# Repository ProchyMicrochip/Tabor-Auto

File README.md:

# Tabor-Auto
Program pro ovládání autíčka přes esp8266 webserver

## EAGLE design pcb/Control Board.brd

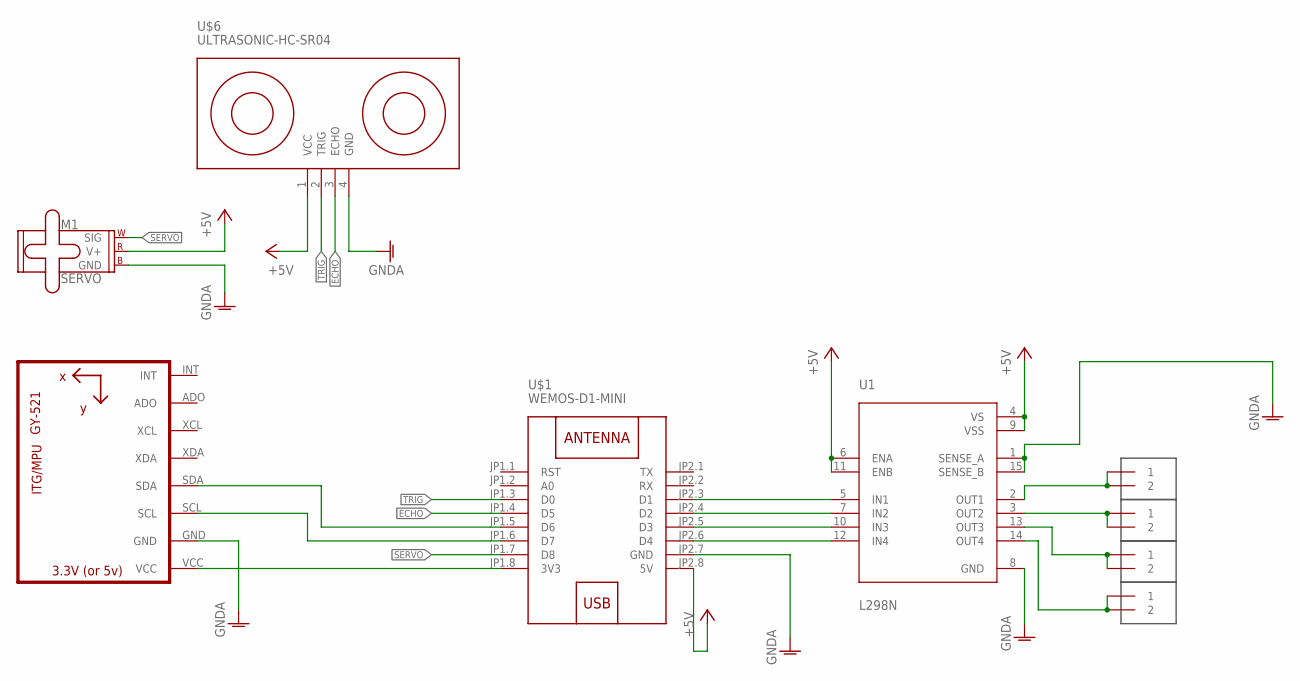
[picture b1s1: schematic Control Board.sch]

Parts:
M1: SERVO; 1X03
U1: L298N; TO127P2020X500X2100-15
U2: GY-521MPU6050; GY-521
U$1: WEMOS-D1-MINI
U$2, U$3, U$4, U$5: TERMINAL_2P; KF301-2P
U$6: ULTRASONIC-HC-SR04

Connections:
+5V: M1.2 (V+), U1.4 (VS), U1.6 (ENA), U1.9 (VSS), U1.11 (ENB), U$1.JP2.8 (5V), U$6.1 (VCC)
ECHO: U$1.JP1.4 (D5), U$6.3 (ECHO)
GNDA: M1.3 (GND), U1.1 (SENSE_A), U1.8 (GND), U1.15 (SENSE_B), U2.GND, U$1.JP2.7 (GND), U$6.4 (GND)
unnamed: U1.5 (IN1), U$1.JP2.3 (D1)
unnamed: U1.7 (IN2), U$1.JP2.4 (D2)
unnamed: U1.10 (IN3), U$1.JP2.5 (D3)
unnamed: U1.12 (IN4), U$1.JP2.6 (D4)
unnamed: U2.VCC, U$1.JP1.8 (3V3)
unnamed: U2.SCL, U$1.JP1.6 (D7)
unnamed: U2.SDA, U$1.JP1.5 (D6)
unnamed: U1.14 (OUT4), U$5.1, U$5.2
unnamed: U1.13 (OUT3), U$4.1, U$4.2
unnamed: U1.3 (OUT2), U$3.1, U$3.2
unnamed: U1.2 (OUT1), U$2.1, U$2.2
SERVO: M1.1 (SIG), U$1.JP1.7 (D8)
TRIG: U$1.JP1.3 (D0), U$6.2 (TRIG)

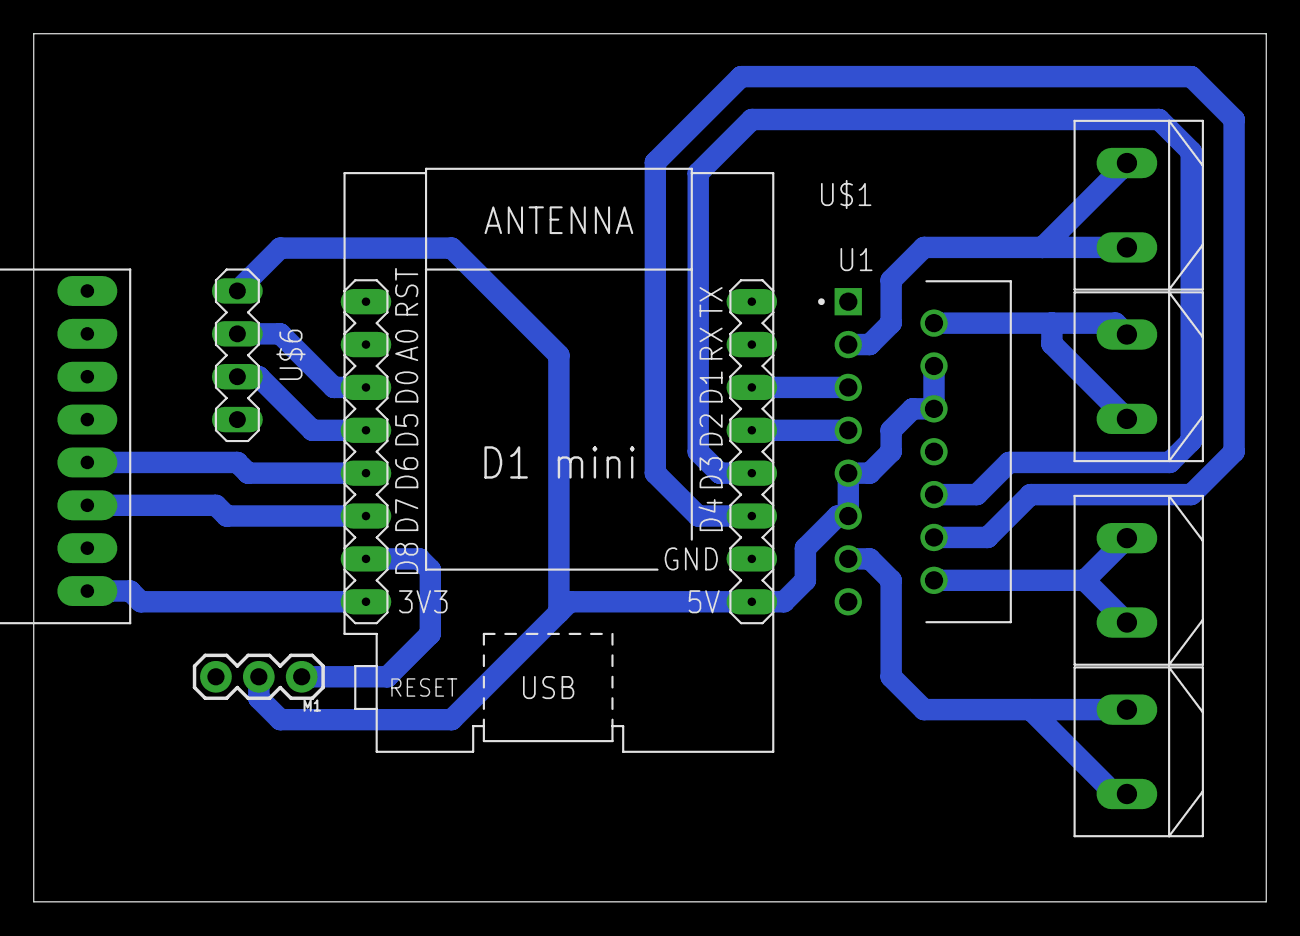
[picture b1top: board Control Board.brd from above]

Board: 2 copper layers, 73.0 x 51.4 mm, 9 parts (0 on the bottom side), 16 nets.

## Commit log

2023-07-07 Initial platformio commit

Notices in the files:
parts and their libraries:
SparkFun-Electromechanical: Licensing: Creative Commons ShareAlike 4.0 International - https://creativecommons.org/licenses/by-sa/4.0
diy-modules: Released under the Creative Commons Attribution 4.0 International License: http://creativecommons.org/licenses/by/4.0
